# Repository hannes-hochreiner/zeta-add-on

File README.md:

# zeta-add-on
An raspberry pi add-on board for the zeta RF module

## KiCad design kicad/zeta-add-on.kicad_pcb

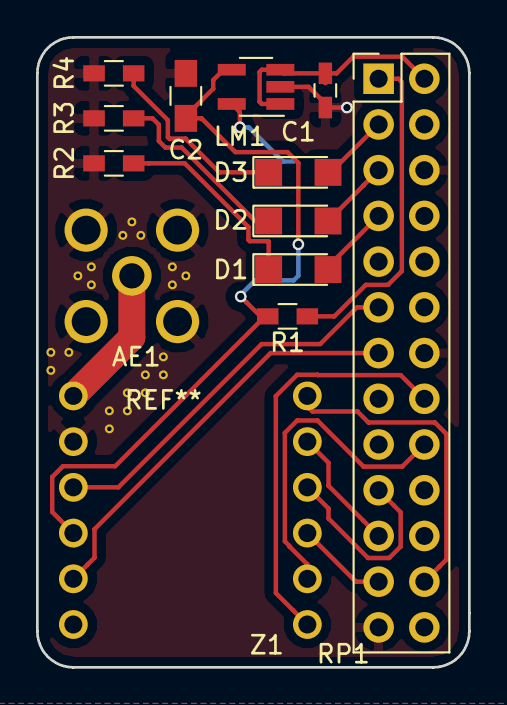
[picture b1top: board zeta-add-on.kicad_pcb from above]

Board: 2 copper layers, 24.0 x 35.0 mm, 14 parts (1 on the bottom side), 20 nets.

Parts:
AE1: Antenna_Shield; SMA
C1: 4.7µF; C_0603_HandSoldering
C2: 10µF; C_0805_HandSoldering
D1, D2, D3: LED; LED_1206
L1: 10µH; INDUCTOR
LM1: LM3670; SOT-23-5_HandSoldering
R1: 0; R_0603_HandSoldering
R2, R3, R4: 50; R_0603_HandSoldering
RP1: RaspberryPi; Pin_Header_Straight_2x13_Pitch2.54mm
Z1: ZETA

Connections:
/3V3: C2.1, L1.1, LM1.4, R1.2, Z1.4
/5V: C1.1, LM1.1, LM1.3, RP1.2
/GPIO1: RP1.18, Z1.8
/GPIO2: RP1.16, Z1.7
/LED1: D1.2, RP1.7
/LED2: D2.2, RP1.5
/LED3: D3.2, RP1.3
GND: AE1.2, C1.2, C2.2, LM1.2, R2.1, R3.1, R4.1, RP1.6, RP1.9, RP1.14, RP1.20, RP1.25, Z1.2
unnamed: AE1.1, Z1.1
unnamed: D1.1, R2.2
unnamed: D2.1, R3.2
unnamed: D3.1, R4.2
unnamed: L1.2, LM1.5
unnamed: R1.1, RP1.1
unnamed: RP1.11, Z1.3
unnamed: RP1.13, Z1.5
unnamed: RP1.19, Z1.10
unnamed: RP1.21, Z1.11
unnamed: RP1.23, Z1.9
unnamed: RP1.24, Z1.12

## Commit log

2017-08-06 added zeta module
2017-08-08 added raspi connector
2017-08-09 added dc-dc-converter
2017-08-12 added LEDs and finished BOM
2017-08-12 started assigning footprints
2017-08-12 started layout
2017-08-13 finished board
2017-08-13 changed the LED resistor and added the color as the LED value
